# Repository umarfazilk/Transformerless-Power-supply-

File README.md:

# Transformerless Power Supply PCB

This project is a **Transformerless Power Supply PCB design** created using **KiCad**. The objective of this project is to design a compact AC-to-DC power supply circuit without using a bulky step-down transformer.

> ⚠️ **Safety Warning**
> Transformerless power supplies are **not isolated from AC mains**. This circuit can be dangerous and may cause electric shock if handled incorrectly. This project is intended only for educational PCB design and simulation study. Do not touch, test, or power the circuit directly without proper supervision, isolation, fuse protection, and safety precautions.

---

## Project Overview

A transformerless power supply converts high-voltage AC mains into low-voltage DC using passive components such as capacitors, resistors, diodes, and voltage regulation components. This type of supply is commonly used in low-current applications where compact size and low cost are important.

This PCB was designed to understand:

* AC-to-DC conversion
* Capacitive dropper power supply concept
* Rectification and filtering
* Voltage regulation
* PCB layout design using KiCad
* Electrical safety spacing and component placement

---

## Problem Statement

Traditional transformer-based power supplies are bulky and expensive for small low-power circuits. For compact low-current applications, a transformerless power supply can reduce size and cost.

The goal of this project is to design a PCB for a simple transformerless power supply and understand the practical design considerations involved in AC mains-based circuits.

---

## Features

* Compact PCB design
* Transformerless AC-to-DC conversion
* Capacitive voltage dropping
* Bridge rectifier-based AC rectification
* Filter capacitor for DC smoothing
* Voltage regulation stage
* Designed using KiCad
* Suitable for educational PCB design practice

---

## Tools Used

* KiCad
* Schematic Design
* PCB Layout Design
* Electrical Rule Check
* Design Rule Check
* Git and GitHub for version control

---

## Project Files

```text
Transformerless-Power-supply/
│
├── README.md
├── Transformerless power supply.kicad_pro
├── Transformerless power supply.kicad_sch
├── Transformerless power supply.kicad_pcb
└── .gitignore
```

---

## File Description

| File                                     | Description                                                 |
| ---------------------------------------- | ----------------------------------------------------------- |
| `Transformerless power supply.kicad_pro` | KiCad project file                                          |
| `Transformerless power supply.kicad_sch` | Schematic design file                                       |
| `Transformerless power supply.kicad_pcb` | PCB layout file                                             |
| `.gitignore`                             | Prevents unwanted KiCad temporary files from being uploaded |
| `README.md`                              | Project documentation                                       |

---

## Basic Working Principle

The circuit works in the following stages:

1. **AC Input Stage**
   The circuit receives AC mains input.

2. **Capacitive Dropper Stage**
   A high-voltage capacitor limits the current by capacitive reactance instead of using a transformer.

3. **Rectifier Stage**
   Diodes convert AC into pulsating DC.

4. **Filtering Stage**
   A capacitor smooths the pulsating DC output.

5. **Voltage Regulation Stage**
   A Zener diode or regulator limits the output voltage to a safer fixed DC level.

6. **Output Stage**
   The regulated DC output can be used for very low-current applications.

---

## Applications

* Low-power indicator circuits
* Small control circuits
* LED driver circuits
* Relay trigger circuits
* Educational power supply design study
* PCB design practice for AC circuits

---

## Important Design Considerations

* Maintain proper clearance between AC and DC sections
* Use high-voltage-rated capacitors
* Add fuse protection at input
* Use discharge resistor across dropper capacitor
* Avoid touching the circuit when powered
* Do not connect this circuit directly to USB, laptop, Arduino, ESP32, or any human-accessible device
* Use an isolation transformer while testing
* Enclose the circuit properly if practically implemented

---

## Limitations

* No galvanic isolation from AC mains
* Dangerous for direct human interaction
* Not suitable for high-current loads
* Output current is limited
* Poor safety compared to transformer-based or SMPS designs
* Not recommended for beginner-level live testing

---

## Future Improvements

* Add fuse protection
* Add MOV for surge protection
* Add proper silkscreen safety markings
* Increase PCB clearance for mains voltage
* Add enclosure design
* Add test points
* Add output LED indicator
* Compare with isolated SMPS-based design

---

## Project Status

This is Version 1 of the PCB design. The current focus is on understanding transformerless power supply design, PCB layout practice, and GitHub project documentation.

---

## Author

**Umar Fazil K**
Electronics and Communication Engineering
Madras Institute of Technology, Anna University

GitHub: [umarfazilk](https://github.com/umarfazilk)
LinkedIn: [linkedin.com/in/umarfazilk](https://linkedin.com/in/umarfazilk)

---

## Disclaimer

This project involves AC mains voltage concepts. It is shared only for learning and documentation purposes. The author is not responsible for damage, injury, or unsafe usage caused by practical implementation of this circuit.

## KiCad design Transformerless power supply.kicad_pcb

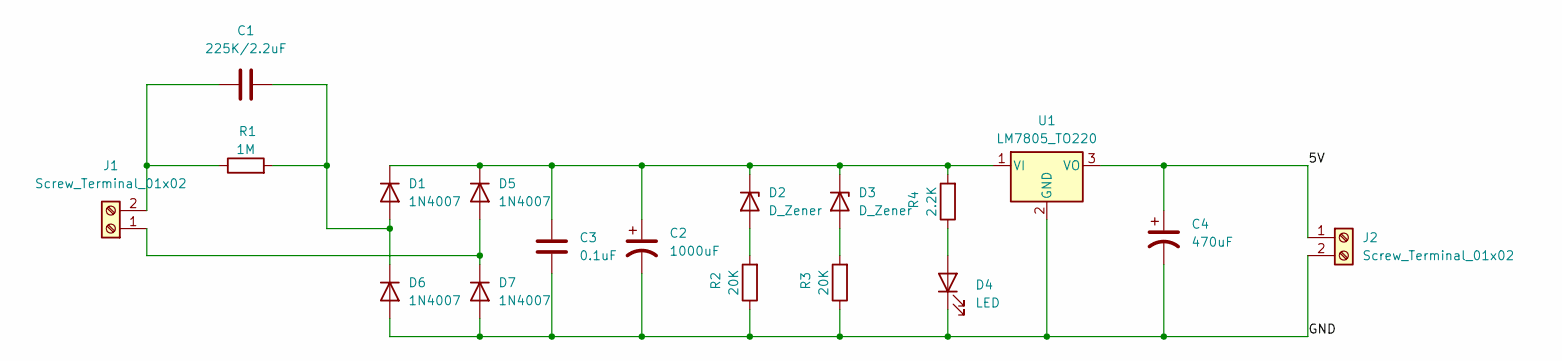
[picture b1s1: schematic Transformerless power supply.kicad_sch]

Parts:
C1: 225K/2.2uF; C_Rect_L18.0mm_W6.0mm_P15.00mm_FKS3_FKP3
C2: 1000uF; CP_Radial_D10.0mm_P3.80mm
C3: 0.1uF; C_Disc_D4.7mm_W2.5mm_P5.00mm
C4: 470uF; CP_Radial_D10.0mm_P5.00mm
D1, D5, D6, D7: 1N4007; D_A-405_P10.16mm_Horizontal
D2, D3: D_Zener; D_DO-34_SOD68_P7.62mm_Horizontal
D4: LED; LED_D5.0mm
J1, J2: Screw_Terminal_01x02; TerminalBlock_Phoenix_PT-1,5-2-5.0-H_1x02_P5.00mm_Horizontal
R1: 1M; R_Axial_DIN0204_L3.6mm_D1.6mm_P5.08mm_Horizontal
R2, R3: 20K; R_Axial_DIN0204_L3.6mm_D1.6mm_P5.08mm_Horizontal
R4: 2.2K; R_Axial_DIN0204_L3.6mm_D1.6mm_P5.08mm_Horizontal
U1: LM7805_TO220; TO-220-3_Vertical

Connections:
/5V: C4.1, J2.1, U1.3 (VO)
/GND: C2.2, C3.1, C4.2, D4.1 (K), D6.2 (A), D7.2 (A), J2.2, R2.1, R3.1, U1.2 (GND)
unnamed: C1.2, D1.2 (A), D6.1 (K), R1.2
unnamed: C2.1, C3.2, D1.1 (K), D2.1 (K), D3.1 (K), D5.1 (K), R4.2, U1.1 (VI)
unnamed: D2.2 (A), R2.2
unnamed: D3.2 (A), R3.2
unnamed: D4.2 (A), R4.1
unnamed: D5.2 (A), D7.1 (K), J1.1
unnamed: C1.1, J1.2, R1.1

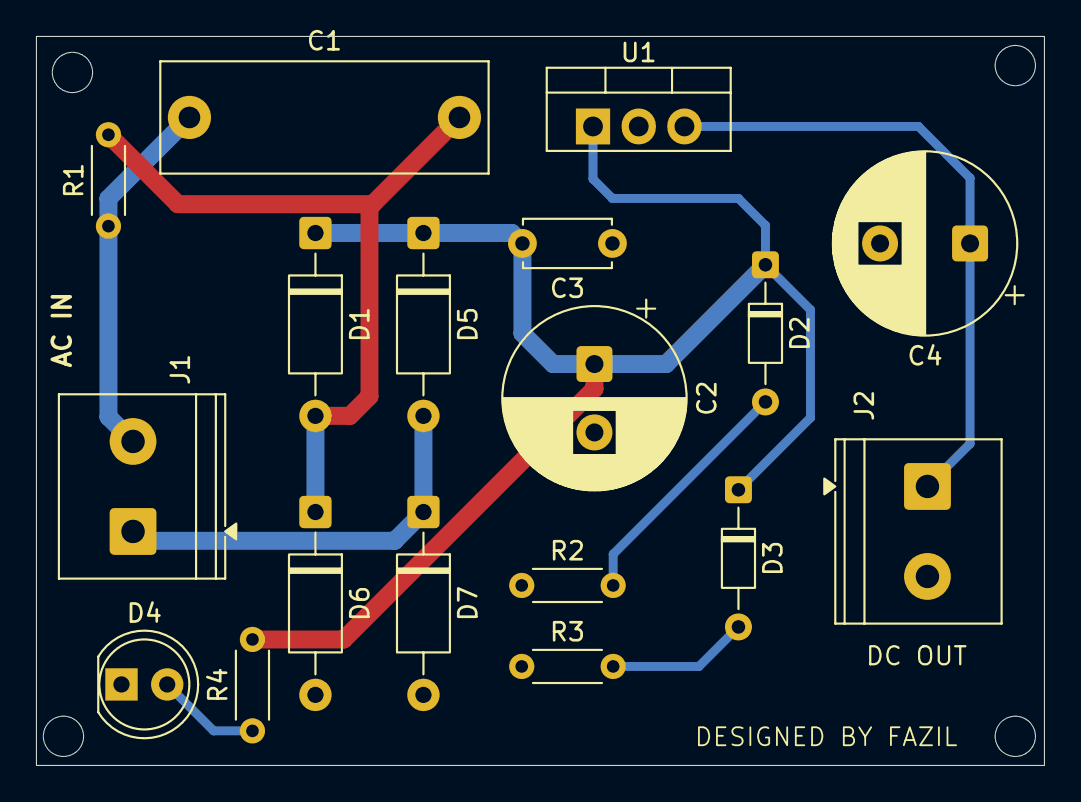
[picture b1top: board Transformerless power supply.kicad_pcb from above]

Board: 2 copper layers, 56.0 x 40.5 mm, 18 parts (0 on the bottom side), 9 nets.

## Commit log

2026-06-13 remove unwanted
2026-06-22 Add new files
